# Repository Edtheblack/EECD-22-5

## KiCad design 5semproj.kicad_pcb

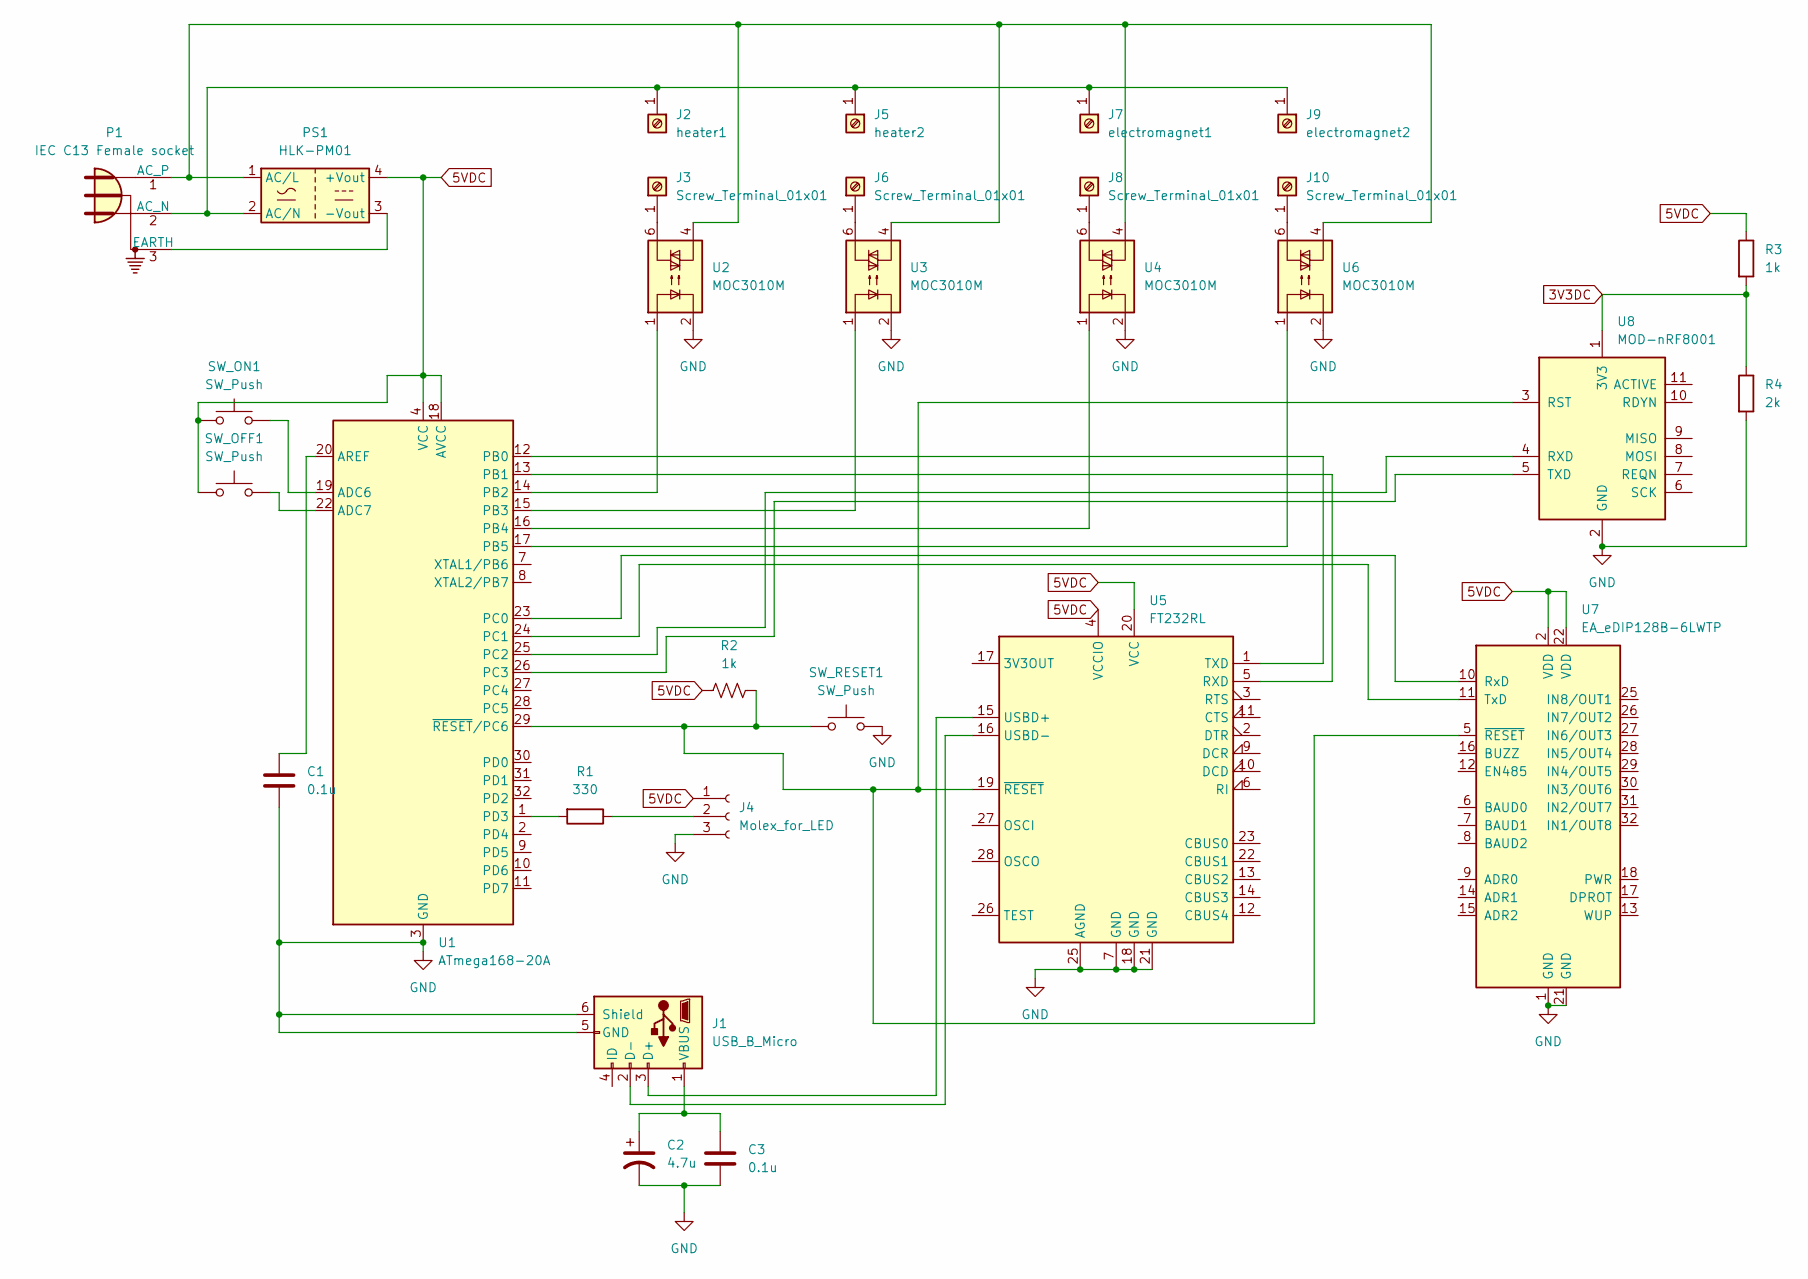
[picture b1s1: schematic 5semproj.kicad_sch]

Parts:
C1, C3: 0.1u; C_0402_1005Metric
C2: 4.7u; CP_Elec_3x5.3
J1: USB_B_Micro; USB_Micro-B_Wuerth_629105150521
J2: heater1; Wuerth_REDCUBE-THR_WP-THRBU_74650073_THR
J3, J6, J8, J10: Screw_Terminal_01x01; Wuerth_REDCUBE-THR_WP-THRBU_74650073_THR
J4: Molex_for_LED; Molex_Micro-Fit_3.0_43650-0300_1x03_P3.00mm_Horizontal
J5: heater2; Wuerth_REDCUBE-THR_WP-THRBU_74650073_THR
J7: electromagnet1; Wuerth_REDCUBE-THR_WP-THRBU_74650073_THR
J9: electromagnet2; Wuerth_REDCUBE-THR_WP-THRBU_74650073_THR
P1: IEC C13 Female socket; PinSocket_1x03_P1.00mm_Vertical
PS1: HLK-PM01; Converter_ACDC_HiLink_HLK-PMxx
R1: 330; R_0402_1005Metric
R2, R3: 1k; R_0402_1005Metric
R4: 2k; R_0402_1005Metric
SW_OFF1: SW_Push; SW_PUSH_6mm_H4.3mm
SW_ON1: SW_Push; SW_PUSH_6mm_H4.3mm
SW_RESET1: SW_Push; SW_PUSH_6mm_H4.3mm
U1: ATmega168-20A; TQFP-32_7x7mm_P0.8mm
U2, U3, U4, U6: MOC3010M; DIP-6_W7.62mm_LongPads
U5: FT232RL; SSOP-28_5.3x10.2mm_P0.65mm
U7: EA_eDIP128B-6LWTP; EA-eDIP128B-XXX
U8: MOD-nRF8001

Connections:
3V3DC: R3.2, R4.1, U8.1 (3V3)
5VDC: J4.1, PS1.4 (+Vout), R2.2, R3.1, SW_OFF1.1, SW_ON1.1, U1.4 (VCC), U1.6 (VCC), U1.18 (AVCC), U5.4 (VCCIO), U5.20 (VCC), U7.2 (VDD), U7.22 (VDD)
GND: C1.2, C2.2, C3.2, J1.5 (GND), J1.6 (Shield), J4.3, R4.2, SW_RESET1.2, U1.3 (GND), U1.5 (GND), U1.21 (GND), U2.2, U3.2, U4.2, U5.7 (GND), U5.18 (GND), U5.21 (GND), U5.25 (AGND), U6.2, U7.1 (GND), U7.21 (GND), U8.2 (GND)
unnamed: C1.1, U1.20 (AREF)
unnamed: C2.1, C3.1, J1.1 (VBUS)
unnamed: J1.2 (D-), U5.16 (USBD-)
unnamed: J1.3 (D+), U5.15 (USBD+)
unnamed: J3.1, U2.6
unnamed: J4.2, R1.1
unnamed: J2.1, J5.1, J7.1, J9.1, P1.2 (AC_N), PS1.2 (AC/N)
unnamed: J6.1, U3.6
unnamed: J8.1, U4.6
unnamed: J10.1, U6.6
unnamed: P1.1 (AC_P), PS1.1 (AC/L), U2.4, U3.4, U4.4, U6.4
unnamed: P1.3 (EARTH), PS1.3 (-Vout)
unnamed: R1.2, U1.1 (PD3)
unnamed: R2.1, SW_RESET1.1, U1.29 (~RESET/PC6), U5.19 (~RESET), U7.5 (~RESET), U8.3 (RST)
unnamed: SW_OFF1.2, U1.22 (ADC7)
unnamed: SW_ON1.2, U1.19 (ADC6)
unnamed: U1.14 (PB2), U2.1
unnamed: U1.15 (PB3), U3.1
unnamed: U1.16 (PB4), U4.1
unnamed: U1.12 (PB0), U5.1 (TXD)
unnamed: U1.13 (PB1), U5.5 (RXD)
unnamed: U1.17 (PB5), U6.1
unnamed: U1.23 (PC0), U7.10 (RxD)
unnamed: U1.24 (PC1), U7.11 (TxD)
unnamed: U1.25 (PC2), U8.4 (RXD)
unnamed: U1.26 (PC3), U8.5 (TXD)

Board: 2 copper layers, 30 parts (0 on the bottom side), 29 nets, no tracks yet.

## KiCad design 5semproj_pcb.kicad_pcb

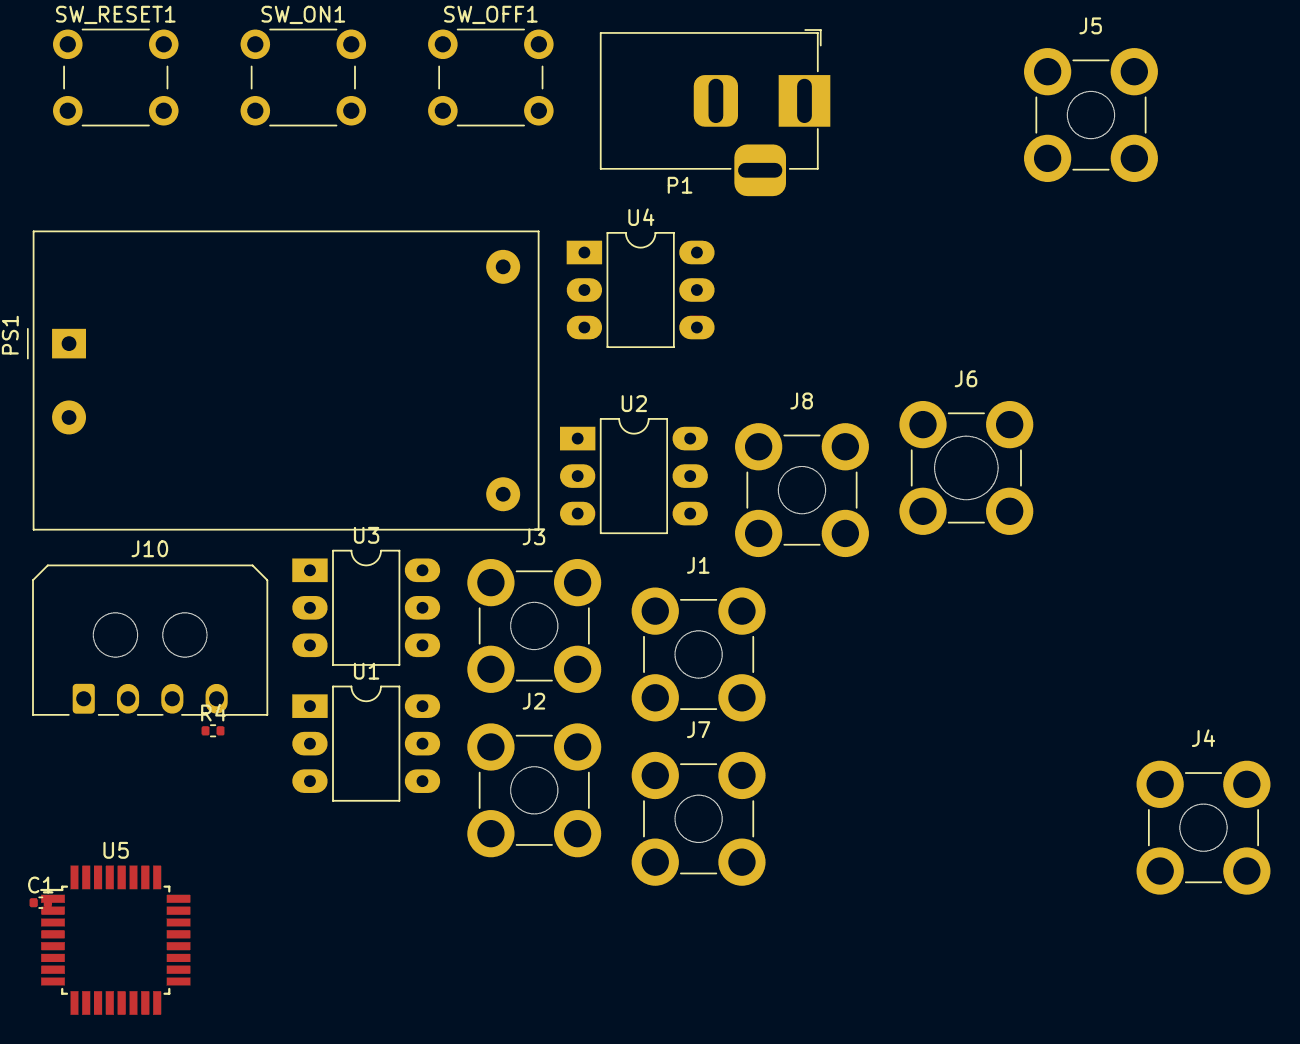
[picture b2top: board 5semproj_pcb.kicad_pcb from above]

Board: 2 copper layers, 21 parts (0 on the bottom side), 18 nets, no tracks yet.

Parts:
C1: 10u; C_0402_1005Metric
J1, J3, J8: Screw_Terminal_01x01; Wuerth_REDCUBE-THR_WP-THRBU_74650073_THR
J2: heater2; Wuerth_REDCUBE-THR_WP-THRBU_74650073_THR
J4: heater1; Wuerth_REDCUBE-THR_WP-THRBU_74650073_THR
J5: electromagnet1; Wuerth_REDCUBE-THR_WP-THRBU_74650073_THR
J6: Screw_Terminal_01x01; Wuerth_REDCUBE-THR_WP-THRBU_74650074_THR
J7: elektromagnet2; Wuerth_REDCUBE-THR_WP-THRBU_74650073_THR
J10: Molex_for_LED; Molex_Micro-Fit_3.0_43650-0400_1x04_P3.00mm_Horizontal
P1: Conn_WallPlug_Earth; BarrelJack_Horizontal
PS1: HLK-PM01; Converter_ACDC_HiLink_HLK-PMxx
R4: 1k; R_0402_1005Metric
SW_OFF1: SW_Push; SW_PUSH_6mm_H4.3mm
SW_ON1: SW_Push; SW_PUSH_6mm_H4.3mm
SW_RESET1: SW_Push; SW_PUSH_6mm_H4.3mm
U1, U2, U3, U4: MOC3010M; DIP-6_W7.62mm_LongPads
U5: ATmega168-20A; TQFP-32_7x7mm_P0.8mm

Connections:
5VDC: PS1.4 (+Vout), R4.2, SW_OFF1.1, SW_ON1.1, U5.4 (VCC), U5.6 (VCC), U5.18 (AVCC)
GND: C1.2, J10.2, SW_RESET1.2, U1.2, U2.2, U3.2, U4.2, U5.3 (GND), U5.5 (GND), U5.21 (GND)
unnamed: C1.1, U5.20 (AREF)
unnamed: J1.1, U2.6
unnamed: J2.1, J4.1, J5.1, J7.1, P1.2 (AC_N), PS1.2 (AC/N)
unnamed: J3.1, U1.6
unnamed: J6.1, U3.6
unnamed: J8.1, U4.6
unnamed: J10.1, U5.32 (PD2)
unnamed: P1.3 (EARTH), PS1.3 (-Vout)
unnamed: R4.1, SW_RESET1.1, U5.29 (~RESET/PC6)
unnamed: SW_OFF1.2, U5.22 (ADC7)
unnamed: SW_ON1.2, U5.19 (ADC6)
unnamed: U1.1, U5.14 (PB2)
unnamed: P1.1 (AC_P), PS1.1 (AC/L), U1.4, U2.4, U3.4, U4.4
unnamed: U2.1, U5.15 (PB3)
unnamed: U3.1, U5.16 (PB4)
unnamed: U4.1, U5.17 (PB5)
